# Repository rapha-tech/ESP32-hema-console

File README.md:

# ESP32 hema console
 New PCB for the small console from hema to use an ESP32

## <https://github.com/ducalex/retro-go>
The esp32 uses Retro-go to emulate games

## Side by side comparison with the original one

## Some pictures of the PCB

Known problems :
- The buttons doesn't make great contact compared to the original PCB

Components :
- ESP32 module without PCB antenna
- 1.54 inches IPS 240*240px
- about 3*30*30mm battery or 4*15*30mm

Note : it is almost the same schematic as my Retro-Ruler
## <https://github.com/rapha-tech/Retro-Ruler>

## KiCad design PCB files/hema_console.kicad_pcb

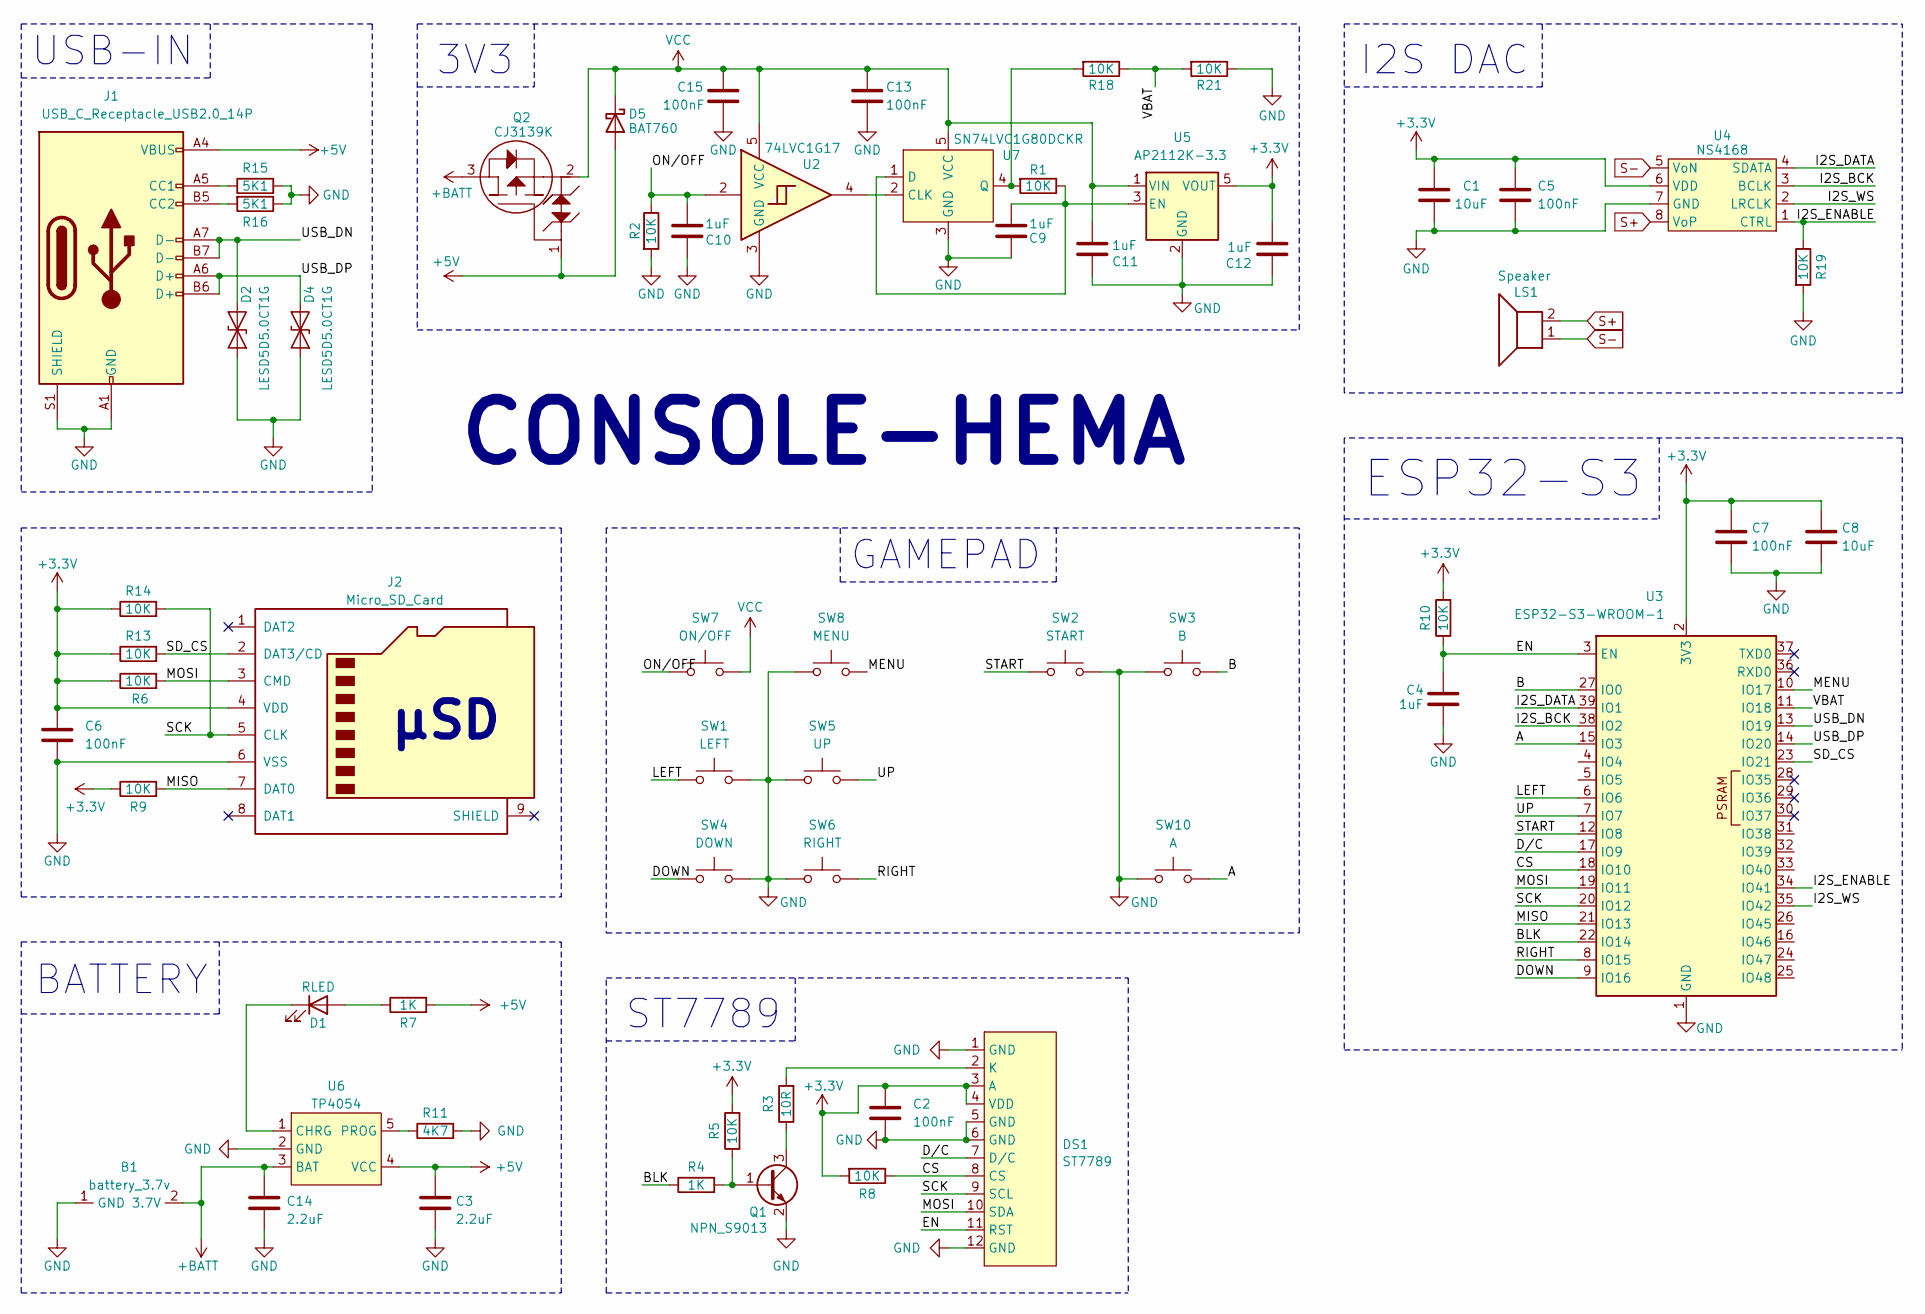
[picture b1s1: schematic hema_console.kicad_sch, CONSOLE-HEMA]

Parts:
B1: battery_3.7v; BAT
C1, C8: 10uF; C_0805_2012Metric
C2, C5, C6, C7, C13, C15: 100nF; C_0603_1608Metric
C3, C14: 2.2uF; C_0603_1608Metric
C4, C9, C10, C11, C12: 1uF; C_0603_1608Metric
D1: RLED; LED_0603_1608Metric
D2, D4: LESD5D5.0CT1G; D_SOD-523
D5: BAT760; D_SOD-323_HandSoldering
DS1: ST7789; ST7789-320x240
J1: USB_C_Receptacle_USB2.0_14P; USB_C_Receptacle_GCT_USB4105-xx-A_16P_TopMnt_Horizontal
J2: Micro_SD_Card; micro_sd
LS1: Speaker; BAT
Q1: NPN_S9013; SOT-23
Q2: CJ3139K; SOT-723
R1, R2, R5, R6, R8, R9, R10, R13, R14, R18, R19, R21: 10K; R_0603_1608Metric
R3: 10R; R_0603_1608Metric
R4, R7: 1K; R_0603_1608Metric
R11: 4K7; R_0603_1608Metric
R15, R16: 5K1; R_0603_1608Metric
SW1: LEFT; Membrane Button Hema Console
SW2: START; Membrane Button Hema Console
SW3: B; Membrane Button Hema Console
SW4: DOWN; Membrane Button Hema Console
SW5: UP; Membrane Button Hema Console
SW6: RIGHT; Membrane Button Hema Console
SW7: ON/OFF; Membrane Button Hema Console
SW8: MENU; Membrane Button Hema Console
SW10: A; Membrane Button Hema Console
U2: 74LVC1G17; SOT-353_SC-70-5
U3: ESP32-S3-WROOM-1
U4: NS4168; HSOP-8-1EP_3.9x4.9mm_P1.27mm_EP2.3x2.3mm
U5: AP2112K-3.3; SOT-23-5
U6: TP4054; SOT-23-5
U7: SN74LVC1G80DCKR; SOT-353_SC-70-5

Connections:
+3.3V: C1.2, C2.1, C5.2, C6.1, C7.1, C8.2, C12.1, DS1.3 (A), DS1.4 (VDD), J2.4 (VDD), R5.2, R6.1, R8.2, R9.1, R10.2, R13.1, R14.1, U3.2 (3V3), U4.6 (VDD), U5.5 (VOUT)
+5V: C3.1, D5.2 (A), J1.A4 (VBUS), J1.A9 (VBUS), J1.B4 (VBUS), J1.B9 (VBUS), Q2.1, R7.2, U6.4 (VCC)
+BATT: B1.2 (3.7V), C14.1, Q2.3, U6.3 (BAT)
/A: SW10.2, U3.15 (IO3)
/B: SW3.2, U3.27 (IO0)
/BLK: R4.1, U3.22 (IO14)
/CS: DS1.8 (CS), R8.1, U3.18 (IO10)
/DOWN: SW4.1, U3.9 (IO16)
/D/C: DS1.7 (D/C), U3.17 (IO9)
/EN: C4.2, DS1.11 (RST), R10.1, U3.3 (EN)
/I2S_BCK: U3.38 (IO2), U4.3 (BCLK)
/I2S_DATA: U3.39 (IO1), U4.4 (SDATA)
/I2S_ENABLE: R19.1, U3.34 (IO41), U4.1 (CTRL)
/I2S_WS: U3.35 (IO42), U4.2 (LRCLK)
/LEFT: SW1.1, U3.6 (IO6)
/MENU: SW8.2, U3.10 (IO17)
/MISO: J2.7 (DAT0), R9.2, U3.21 (IO13)
/MOSI: DS1.10 (SDA), J2.3 (CMD), R6.2, U3.19 (IO11)
/ON/OFF: C10.2, R2.1, SW7.1, U2.2
/RIGHT: SW6.2, U3.8 (IO15)
/SCK: DS1.9 (SCL), J2.5 (CLK), R14.2, U3.20 (IO12)
/SD_CS: J2.2 (DAT3/CD), R13.2, U3.23 (IO21)
/START: SW2.1, U3.12 (IO8)
/UP: SW5.2, U3.7 (IO7)
/USB_DN: D2.2 (A2), J1.A7 (D-), J1.B7 (D-), U3.13 (IO19)
/USB_DP: D4.2 (A2), J1.A6 (D+), J1.B6 (D+), U3.14 (IO20)
/VBAT: R18.1, R21.2, U3.11 (IO18)
GND: B1.1 (GND), C1.1, C2.2, C3.2, C4.1, C5.1, C6.2, C7.2, C8.1, C9.1, C10.1, C11.1, C12.2, C13.2, C14.2, C15.2, D2.1 (A1), D4.1 (A1), DS1.1 (GND), DS1.5 (GND), DS1.6 (GND), DS1.12 (GND), J1.A1 (GND), J1.A12 (GND), J1.B1 (GND), J1.B12 (GND), J1.S1 (SHIELD), J2.6 (VSS), Q1.2 (E), R2.2, R11.2, R15.2, R16.1, R19.2, R21.1, SW1.2, SW2.2, SW3.1, SW4.2, SW5.1, SW6.1, SW8.1, SW10.1, U2.3 (GND), U3.1 (GND), U3.40 (GND), U3.41 (GND), U4.7 (GND), U5.2 (GND), U6.2 (GND), U7.3 (GND)
unnamed: D1.2 (A), R7.1
unnamed: D1.1 (K), U6.1 (CHRG)
unnamed: DS1.2 (K), R3.2
unnamed: J1.A5 (CC1), R15.1
unnamed: J1.B5 (CC2), R16.2
unnamed: Q1.1 (B), R4.2, R5.1
unnamed: Q1.3 (C), R3.1
unnamed: C9.2, R1.1, U5.3 (EN), U7.1 (D)
unnamed: R11.1, U6.5 (PROG)
unnamed: U2.4, U7.2 (CLK)
unnamed: R1.2, R18.2, U7.4 (Q)
S+: LS1.2, U4.8 (VoP); also elsewhere on the board
S-: LS1.1, U4.5 (VoN); also elsewhere on the board
VCC: C11.2, C13.1, C15.1, D5.1 (K), Q2.2, SW7.2, U2.5 (VCC), U5.1 (VIN), U7.5 (VCC)

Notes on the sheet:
BATTERY
I2S DAC
μSD
3V3
GAMEPAD
CONSOLE-HEMA
ESP32-S3
USB-IN
ST7789

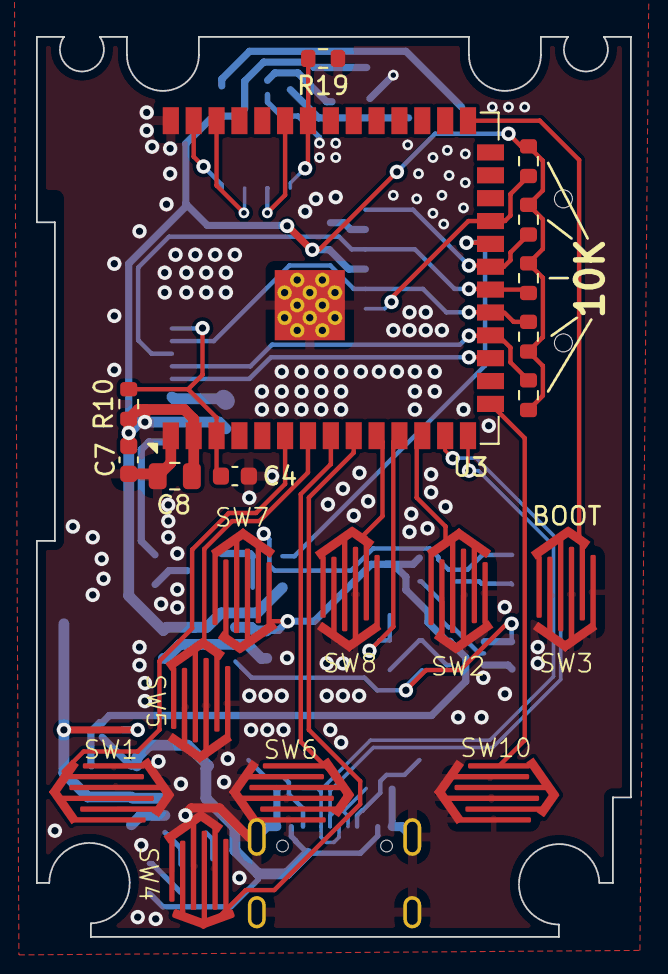
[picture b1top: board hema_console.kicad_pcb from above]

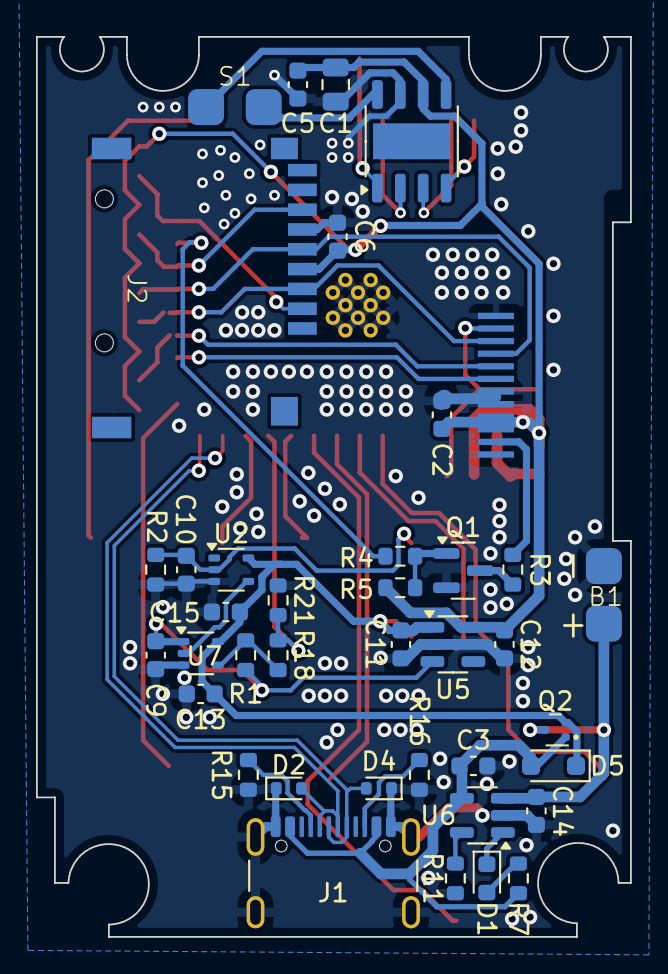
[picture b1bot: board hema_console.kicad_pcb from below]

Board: 2 copper layers, 33.0 x 50.0 mm, 59 parts (39 on the bottom side), 42 nets.

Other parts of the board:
S1: Speaker; BAT

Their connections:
S+: S1.2; also elsewhere on the board
S-: S1.1; also elsewhere on the board

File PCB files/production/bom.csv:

Designator,Footprint,Quantity,Value,LCSC Part #
B1,BAT,1,battery_3.7v,
"C1, C8",0805,2,10uF,
"C10, C11, C12, C4, C9",0603,5,1uF,
"C13, C15, C2, C5, C6, C7",0603,6,100nF,
"C14, C3",0603,2,2.2uF,
D1,0603,1,RLED,
"D2, D4",D_SOD-523,2,LESD5D5.0CT1G,
D5,D_SOD-323_HandSoldering,1,BAT760,
DS1,ST7789-320x240,1,ST7789,
J1,USB_C_Receptacle_GCT_USB4105-xx-A_16P_TopMnt_Horizontal,1,USB_C_Receptacle_USB2.0_14P,
J2,micro_sd,1,Micro_SD_Card,
Q1,SOT-23,1,NPN_S9013,
Q2,SOT-723,1,CJ3139K,
"R1, R10, R13, R14, R18, R19, R2, R21, R5, R6, R8, R9",0603,12,10K,
R11,0603,1,4K7,
"R15, R16",0603,2,5K1,
R3,0603,1,10R,
"R4, R7",0603,2,1K,
S1,BAT,1,Speaker,
SW1,Membrane Button Hema Console,1,LEFT,
SW10,Membrane Button Hema Console,1,A,
SW2,Membrane Button Hema Console,1,START,
SW3,Membrane Button Hema Console,1,B,
SW4,Membrane Button Hema Console,1,DOWN,
SW5,Membrane Button Hema Console,1,UP,
SW6,Membrane Button Hema Console,1,RIGHT,
SW7,Membrane Button Hema Console,1,ON/OFF,
SW8,Membrane Button Hema Console,1,MENU,
U2,SOT-353_SC-70-5,1,74LVC1G17,
U3,ESP32-S3-WROOM-1,1,ESP32-S3-WROOM-1,
U4,HSOP-8-1EP_3.9x4.9mm_P1.27mm_EP2.3x2.3mm,1,NS4168,
U5,SOT-23-5,1,AP2112K-3.3,
U6,SOT-23-5,1,TP4054,
U7,SOT-353_SC-70-5,1,SN74LVC1G80DCKR,

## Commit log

2025-05-06 first commit
    all the files to make and program the new PCB for the small HEMA console
